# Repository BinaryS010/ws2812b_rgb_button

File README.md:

# ws2812b_rgb_button

WS2812B based RGB flipper button adapter for virtual pinball machines.

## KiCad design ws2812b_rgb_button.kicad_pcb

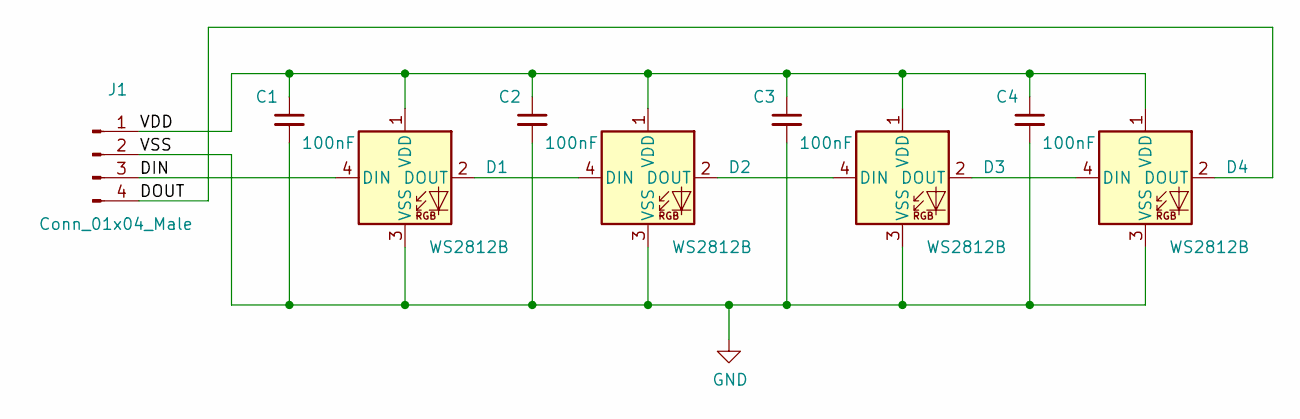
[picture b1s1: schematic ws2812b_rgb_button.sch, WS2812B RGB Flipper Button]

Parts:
C1, C2, C3, C4: 100nF; C_0603_1608Metric
D1, D2, D3, D4: WS2812B; LED_WS2812B_PLCC4_5.0x5.0mm_P3.2mm
J1: Conn_01x04_Male; JST_XH_S04B-XH-A_1x04_P2.50mm_Horizontal

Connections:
/DIN: D1.4 (DIN), J1.3
/DOUT: D4.2 (DOUT), J1.4
/VDD: C1.1, C2.1, C3.1, C4.1, D1.1 (VDD), D2.1 (VDD), D3.1 (VDD), D4.1 (VDD), J1.1
GND: C1.2, C2.2, C3.2, C4.2, D1.3 (VSS), D2.3 (VSS), D3.3 (VSS), D4.3 (VSS), J1.2
unnamed: D1.2 (DOUT), D2.4 (DIN)
unnamed: D2.2 (DOUT), D3.4 (DIN)
unnamed: D3.2 (DOUT), D4.4 (DIN)

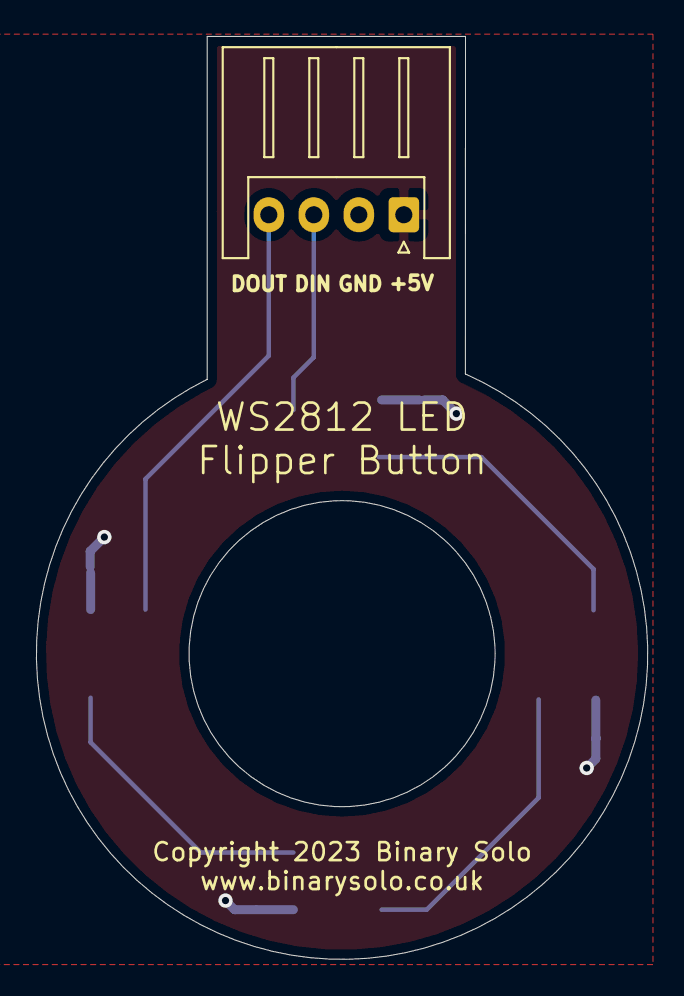
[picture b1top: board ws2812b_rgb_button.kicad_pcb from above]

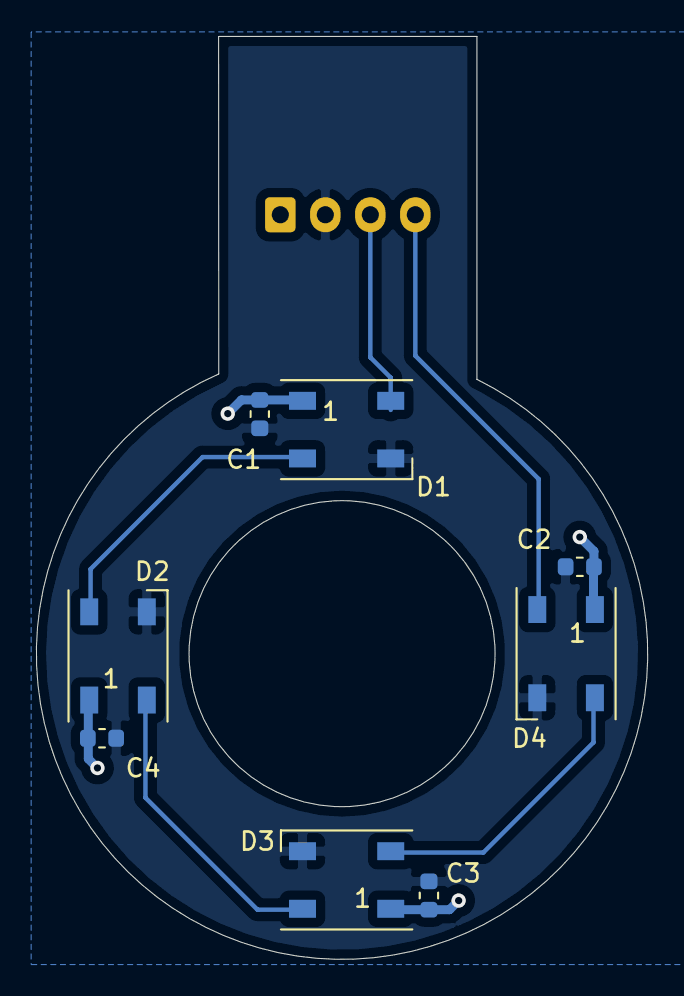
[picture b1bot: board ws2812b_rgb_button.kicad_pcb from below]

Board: 2 copper layers, 34.0 x 51.3 mm, 9 parts (8 on the bottom side), 7 nets.

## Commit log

2023-11-27 Initial commit.
2023-11-27 PCB design files.

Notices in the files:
ws2812b_rgb_button.kicad_pcb:
Copyright 2023 Binary Solo
